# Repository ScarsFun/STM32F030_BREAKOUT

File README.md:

# STM32F030_BREAKOUT
STM32F030 BREAKOUT BOARD

* Eagle PCB, Schematics, gerber files for JLCPCB PCB print service.
* simple Keil RTX blinky LED demo.

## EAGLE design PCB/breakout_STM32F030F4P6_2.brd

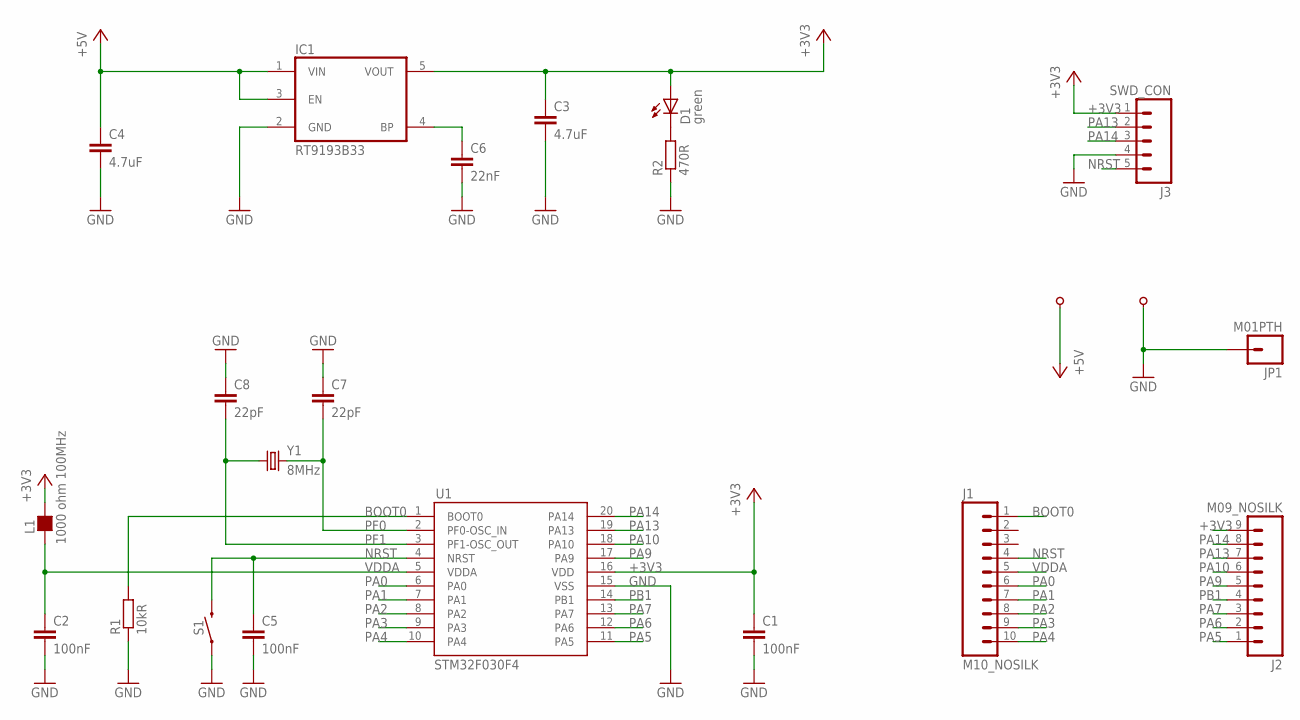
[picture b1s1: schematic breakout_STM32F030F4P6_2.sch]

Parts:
5V: M01_1SQ
C1, C2, C5: 100nF; C0805
C3, C4: 4.7uF; C3216
C6: 22nF; C0805
C7, C8: 22pF; C0805
D1: green; SML0805
GND: M01_NOSILK
IC1: RT9193B33; TSOT23-5
J1: M10_NOSILK
J2: M09_NOSILK
J3: SWD_CON; M05_NOSILK_1SQ
JP1: M01PTH; 1X01
L1: 1000 ohm 100MHz; L0805
R1: 10kR; R0805
R2: 470R; R0805
S1: MOMENTARY-SWITCH-SPST-SMD-5.2MM; TACTILE_SWITCH_SMD_5.2MM
U1: STM32F030F4; TSSOP-20
Y1: 8MHz; CRYSTAL-SMD-5X3

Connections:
+3V3: C1.1, C3.1, D1.A, IC1.5 (VOUT), J2.9, J3.1, L1.2, U1.16 (VDD)
+5V: 5V.1, C4.1, IC1.1 (VIN), IC1.3 (EN)
BOOT0: J1.1, R1.2, U1.1 (BOOT0)
GND: C1.2, C2.2, C3.2, C4.2, C5.2, C6.2, C7.1, C8.1, GND.1, IC1.2 (GND), J3.4, JP1.1, R1.1, R2.1, S1.1, U1.15 (VSS)
unnamed: D1.C, R2.2
unnamed: C6.1, IC1.4 (BP)
NRST: C5.1, J1.4, J3.5, S1.3 (2), U1.4 (NRST)
PA0: J1.6, U1.6 (PA0)
PA1: J1.7, U1.7 (PA1)
PA2: J1.8, U1.8 (PA2)
PA3: J1.9, U1.9 (PA3)
PA4: J1.10, U1.10 (PA4)
PA5: J2.1, U1.11 (PA5)
PA6: J2.2, U1.12 (PA6)
PA7: J2.3, U1.13 (PA7)
PA9: J2.5, U1.17 (PA9)
PA10: J2.6, U1.18 (PA10)
PA13: J2.7, J3.2, U1.19 (PA13)
PA14: J2.8, J3.3, U1.20 (PA14)
PB1: J2.4, U1.14 (PB1)
PF0: C7.2, U1.2 (PF0-OSC_IN), Y1.3 (2)
PF1: C8.2, U1.3 (PF1-OSC_OUT), Y1.1
VDDA: C2.1, J1.5, L1.1, U1.5 (VDDA)

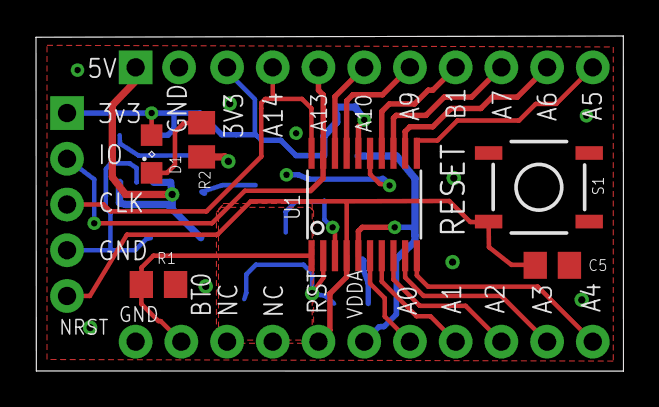
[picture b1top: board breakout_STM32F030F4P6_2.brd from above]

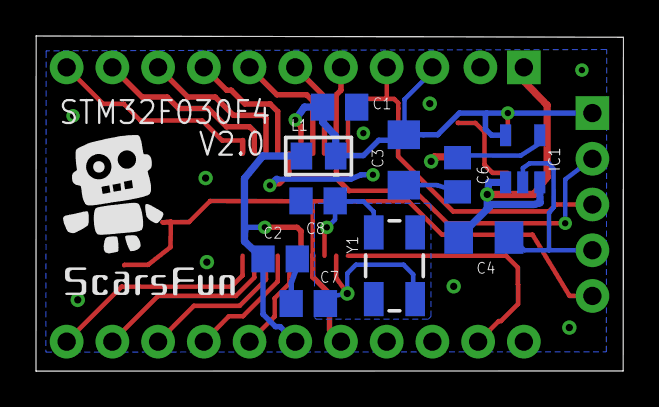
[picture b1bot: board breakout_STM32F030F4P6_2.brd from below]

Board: 2 copper layers, 32.6 x 18.6 mm, 22 parts (10 on the bottom side), 23 nets.

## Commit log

2019-04-02 first release

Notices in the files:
parts and their libraries:
richtek: Copyright (C) 2015, Bob Starr
rc-master: Copyright (C) 2007, Bob Starr
SparkFun: Licensing: CC v3.0 Share-Alike You are welcome to use this library for commercial purposes.
